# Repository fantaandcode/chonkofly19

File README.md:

# chonkofly19
Based on [vlkv's Chocofly](https://github.com/vlkv/chocofly/tree/v3) keyboard layout, made to MX spacing and mounting points to allow for easier Choc V2 switch and MX stem keycap compatibility.

This keyboard is meant to be used with Pi Picos, specifically the YD-RP2040 as it has USB-C.

As is, this is *only* hotswap. If there is enough desire, I'm willing to make a board-soldered version.

## Features
- Kailh Choc V1 and V2 switch compatibility (hotswap)
- 19.05x19.05 MX keycap spacing
- Non-aggressive columnar stagger with fanned 2 outer columns
- 4 thumb key cluster with 2 upper thumb keys

### Chonkofly V1 PCB

## Differences and Why
### No encoders?
This is deliberate as the 2 EVQWGD001 roller encoders that were on the original Chocofly. They are expensive ($20-25 per) and they are not being made anymore. I personally do not use an encoder, but would be open to adding a low-profile rotary encoder. Or an alternative that uses mouse encoders like the ones detailed in [roBa](https://github.com/kumamuk-git/roBa/blob/main/doc/v3/buildguide_v3.md) build guide.

### "Sonshi"?
I certainly understand why vlkv would make the keyboard this way. I use this keyboard as my daily and I didn't like how it looks sitting on my desk without a case. I'm not using it as a keyboard replacement for my laptop, so portability is not as important to me. As a result, a bit of extra PCB has been removed from the sides. Mounting holes have been added for a 3D printed case.

### Wireless?
Since this keyboard is not for my laptop, this does not have a battery and thus doesn't need wireless. This makes the board a lot simpler too. Maybe I'd make a wireless version in the future? I do not know what the state of ZMK is on Pi Pico is at the moment, but I would be willing to look into it in the future.

### To Do
- 3D printed case
- 3D printed wristrest
- MX?
- Board-soldered option?
- Folding? Probably a different design at that rate
- Upload firmware

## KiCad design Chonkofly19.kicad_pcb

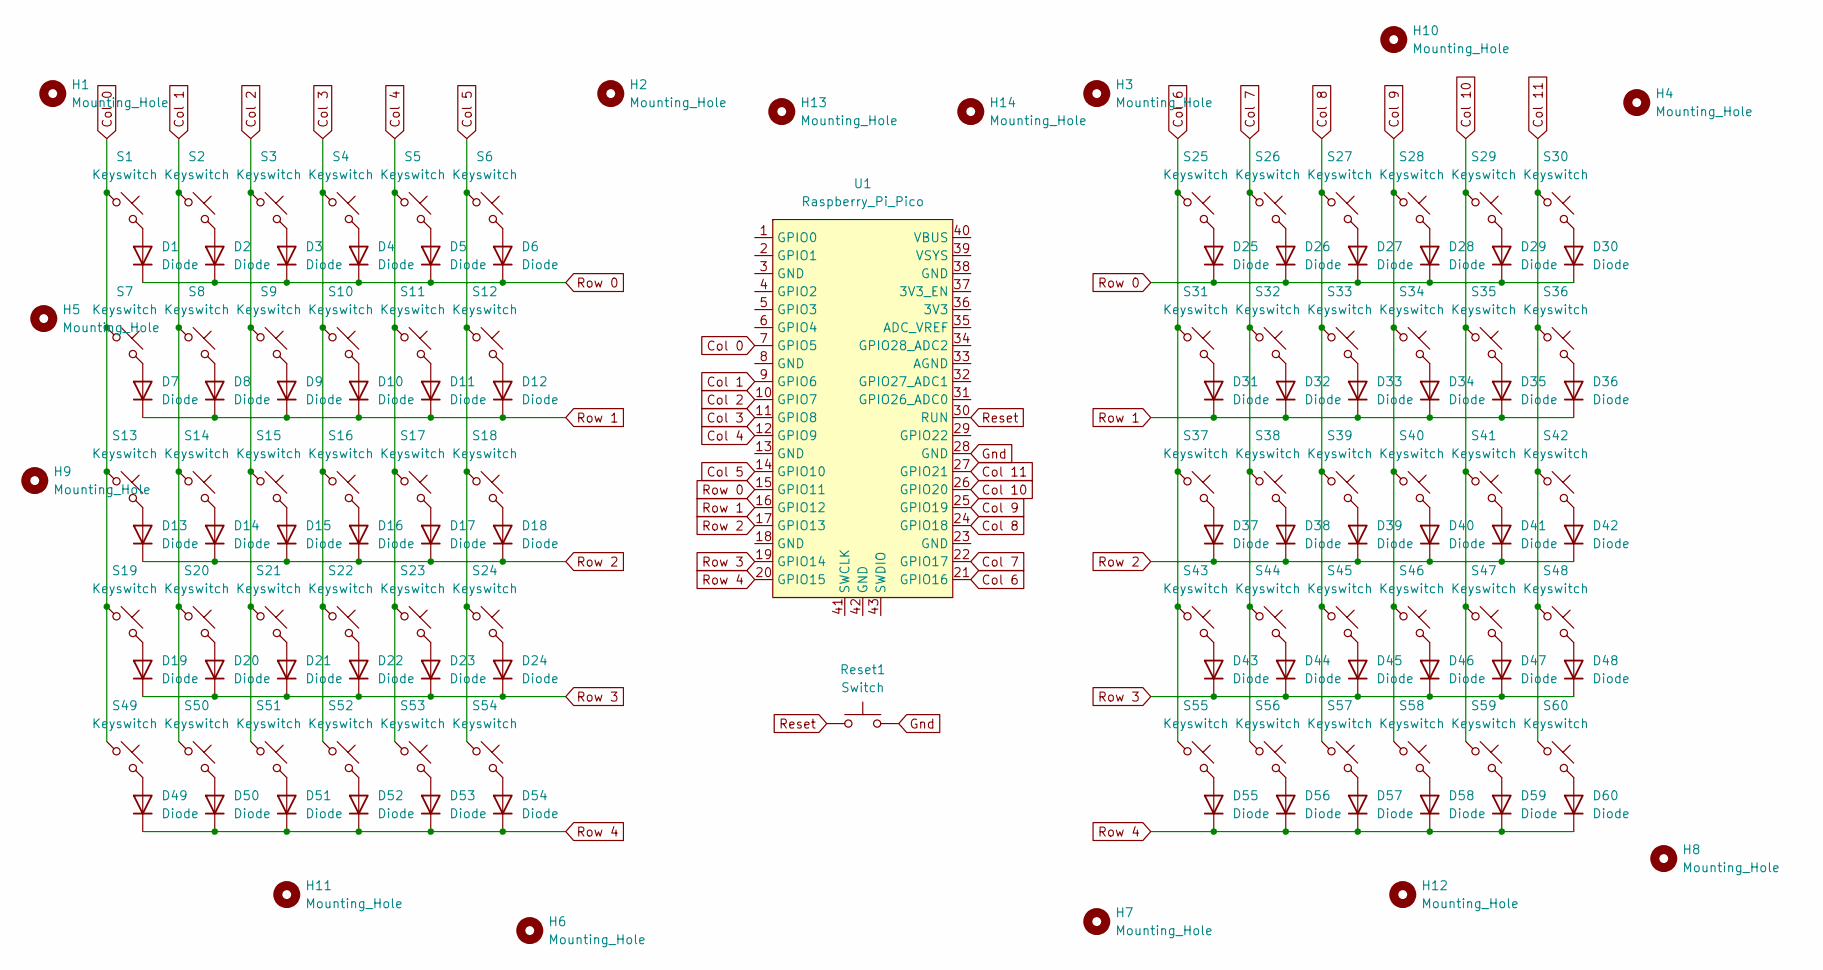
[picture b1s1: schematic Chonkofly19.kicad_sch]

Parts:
D1, D2, D3, D4, D5, D6, D7, D8, D9, D10, D11, D12, D13, D14, D15, D16, D17, D18, D19, D20, D21, D22, D23, D24, D25, D26, D27, D28, D29, D30, D31, D32, D33, D34, D35, D36, D37, D38, D39, D40, D41, D42, D43, D44, D45, D46, D47, D48, D49, D50, D51, D52, D53, D54, D55, D56, D57, D58, D59, D60: Diode; Diode_DO-35
H1, H2, H3, H4, H5, H6, H7, H8, H9, H10, H11, H12, H13, H14: Mounting_Hole; Standoff_M2x4mm
Reset1: Switch; Button_MJTP1243
S1, S2, S3, S4, S5, S6, S7, S8, S9, S10, S11, S12, S13, S14, S15, S16, S17, S18, S19, S20, S21, S22, S23, S24, S25, S26, S27, S28, S29, S30, S31, S32, S33, S34, S35, S36, S37, S38, S39, S40, S41, S42, S43, S44, S45, S46, S47, S48, S49, S50, S51, S52, S53, S54, S55, S56, S57, S58, S59, S60: Keyswitch; Hotswap_Choc_V1V2_1.00u
U1: Raspberry_Pi_Pico

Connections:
Col 0: S1.1, S7.1, S13.1, S19.1, S49.1, U1.7 (GPIO5)
Col 1: S2.1, S8.1, S14.1, S20.1, S50.1, U1.9 (GPIO6)
Col 2: S3.1, S9.1, S15.1, S21.1, S51.1, U1.10 (GPIO7)
Col 3: S4.1, S10.1, S16.1, S22.1, S52.1, U1.11 (GPIO8)
Col 4: S5.1, S11.1, S17.1, S23.1, S53.1, U1.12 (GPIO9)
Col 5: S6.1, S12.1, S18.1, S24.1, S54.1, U1.14 (GPIO10)
Col 6: S25.1, S31.1, S37.1, S43.1, S55.1, U1.21 (GPIO16)
Col 7: S26.1, S32.1, S38.1, S44.1, S56.1, U1.22 (GPIO17)
Col 8: S27.1, S33.1, S39.1, S45.1, S57.1, U1.24 (GPIO18)
Col 9: S28.1, S34.1, S40.1, S46.1, S58.1, U1.25 (GPIO19)
Col 10: S29.1, S35.1, S41.1, S47.1, S59.1, U1.26 (GPIO20)
Col 11: S30.1, S36.1, S42.1, S48.1, S60.1, U1.27 (GPIO21)
Gnd: Reset1.2, U1.28 (GND)
unnamed: D1.2 (A), S1.2
unnamed: D2.2 (A), S2.2
unnamed: D3.2 (A), S3.2
unnamed: D4.2 (A), S4.2
unnamed: D5.2 (A), S5.2
unnamed: D6.2 (A), S6.2
unnamed: D7.2 (A), S7.2
unnamed: D8.2 (A), S8.2
unnamed: D9.2 (A), S9.2
unnamed: D10.2 (A), S10.2
unnamed: D11.2 (A), S11.2
unnamed: D12.2 (A), S12.2
unnamed: D13.2 (A), S13.2
unnamed: D14.2 (A), S14.2
unnamed: D15.2 (A), S15.2
unnamed: D16.2 (A), S16.2
unnamed: D17.2 (A), S17.2
unnamed: D18.2 (A), S18.2
unnamed: D19.2 (A), S19.2
unnamed: D20.2 (A), S20.2
unnamed: D21.2 (A), S21.2
unnamed: D22.2 (A), S22.2
unnamed: D23.2 (A), S23.2
unnamed: D24.2 (A), S24.2
unnamed: D25.2 (A), S25.2
unnamed: D26.2 (A), S26.2
unnamed: D27.2 (A), S27.2
unnamed: D28.2 (A), S28.2
unnamed: D29.2 (A), S29.2
unnamed: D30.2 (A), S30.2
unnamed: D31.2 (A), S31.2
unnamed: D32.2 (A), S32.2
unnamed: D33.2 (A), S33.2
unnamed: D34.2 (A), S34.2
unnamed: D35.2 (A), S35.2
unnamed: D36.2 (A), S36.2
unnamed: D37.2 (A), S37.2
unnamed: D38.2 (A), S38.2
unnamed: D39.2 (A), S39.2
unnamed: D40.2 (A), S40.2
unnamed: D41.2 (A), S41.2
unnamed: D42.2 (A), S42.2
unnamed: D43.2 (A), S43.2
unnamed: D44.2 (A), S44.2
unnamed: D45.2 (A), S45.2
unnamed: D46.2 (A), S46.2
unnamed: D47.2 (A), S47.2
unnamed: D48.2 (A), S48.2
unnamed: D49.2 (A), S49.2
unnamed: D50.2 (A), S50.2
unnamed: D51.2 (A), S51.2
unnamed: D52.2 (A), S52.2
unnamed: D53.2 (A), S53.2
unnamed: D54.2 (A), S54.2
unnamed: D55.2 (A), S55.2
unnamed: D56.2 (A), S56.2
unnamed: D57.2 (A), S57.2
unnamed: D58.2 (A), S58.2
unnamed: D59.2 (A), S59.2
unnamed: D60.2 (A), S60.2
Reset: Reset1.1, U1.30 (RUN)
Row 0: D1.1 (K), D2.1 (K), D3.1 (K), D4.1 (K), D5.1 (K), D6.1 (K), D25.1 (K), D26.1 (K), D27.1 (K), D28.1 (K), D29.1 (K), D30.1 (K), U1.15 (GPIO11)
Row 1: D7.1 (K), D8.1 (K), D9.1 (K), D10.1 (K), D11.1 (K), D12.1 (K), D31.1 (K), D32.1 (K), D33.1 (K), D34.1 (K), D35.1 (K), D36.1 (K), U1.16 (GPIO12)
Row 2: D13.1 (K), D14.1 (K), D15.1 (K), D16.1 (K), D17.1 (K), D18.1 (K), D37.1 (K), D38.1 (K), D39.1 (K), D40.1 (K), D41.1 (K), D42.1 (K), U1.17 (GPIO13)
Row 3: D19.1 (K), D20.1 (K), D21.1 (K), D22.1 (K), D23.1 (K), D24.1 (K), D43.1 (K), D44.1 (K), D45.1 (K), D46.1 (K), D47.1 (K), D48.1 (K), U1.19 (GPIO14)
Row 4: D49.1 (K), D50.1 (K), D51.1 (K), D52.1 (K), D53.1 (K), D54.1 (K), D55.1 (K), D56.1 (K), D57.1 (K), D58.1 (K), D59.1 (K), D60.1 (K), U1.20 (GPIO15)

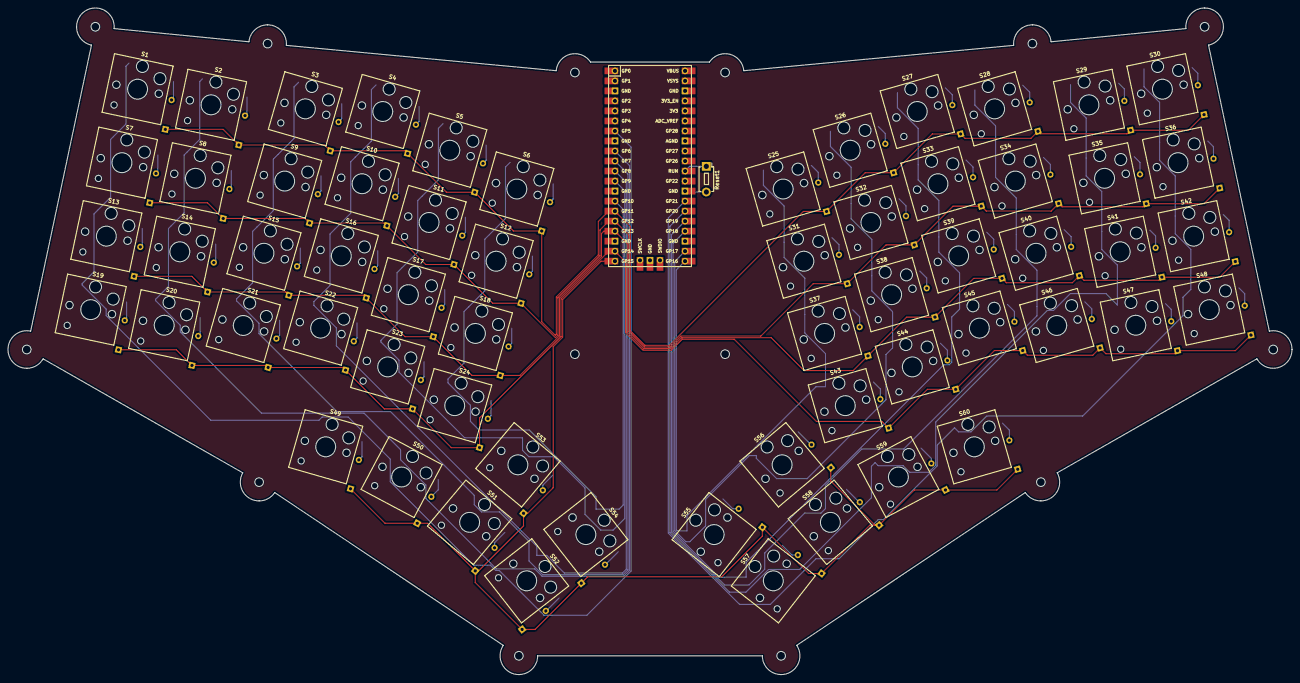
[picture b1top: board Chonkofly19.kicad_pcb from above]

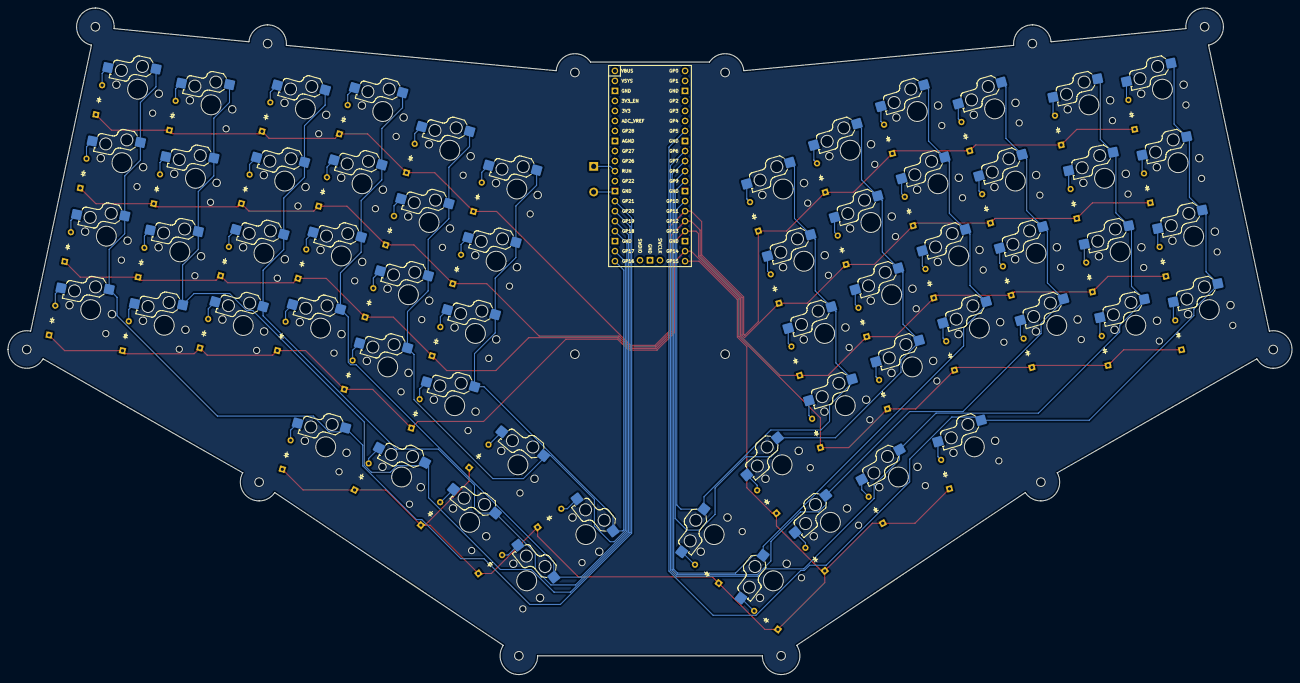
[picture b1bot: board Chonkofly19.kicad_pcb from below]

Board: 2 copper layers, 325.6 x 169.0 mm, 136 parts (60 on the bottom side), 79 nets.

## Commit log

2025-07-14 First iteration
2025-07-14 v1.0 production finish
2025-07-19 Update README.md
    Added PCB footprint
2025-07-19 Create LICENSE
2025-07-20 Added step file
2025-07-23 Add plate edge cut
2025-12-16 Added edge cuts for v1
